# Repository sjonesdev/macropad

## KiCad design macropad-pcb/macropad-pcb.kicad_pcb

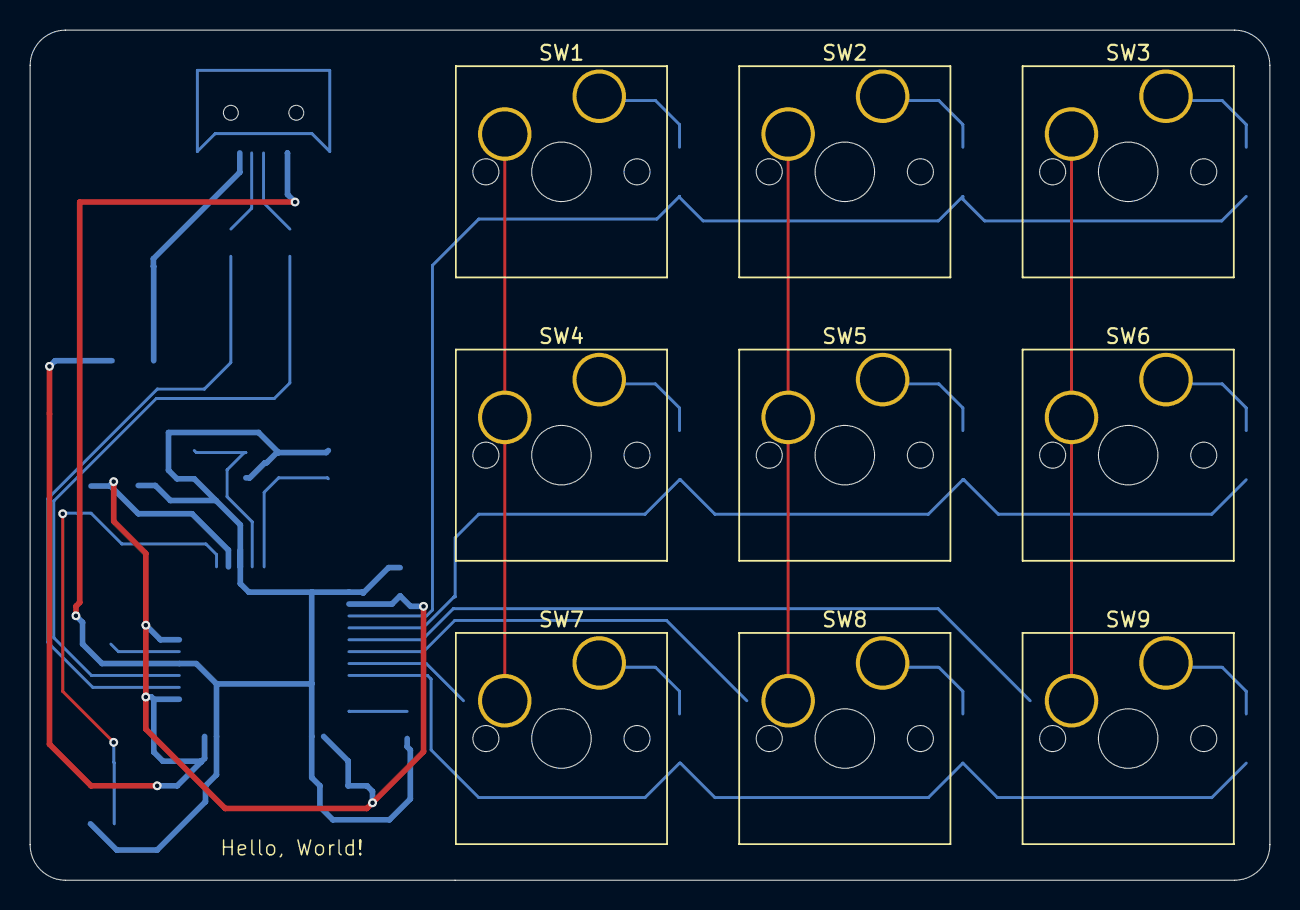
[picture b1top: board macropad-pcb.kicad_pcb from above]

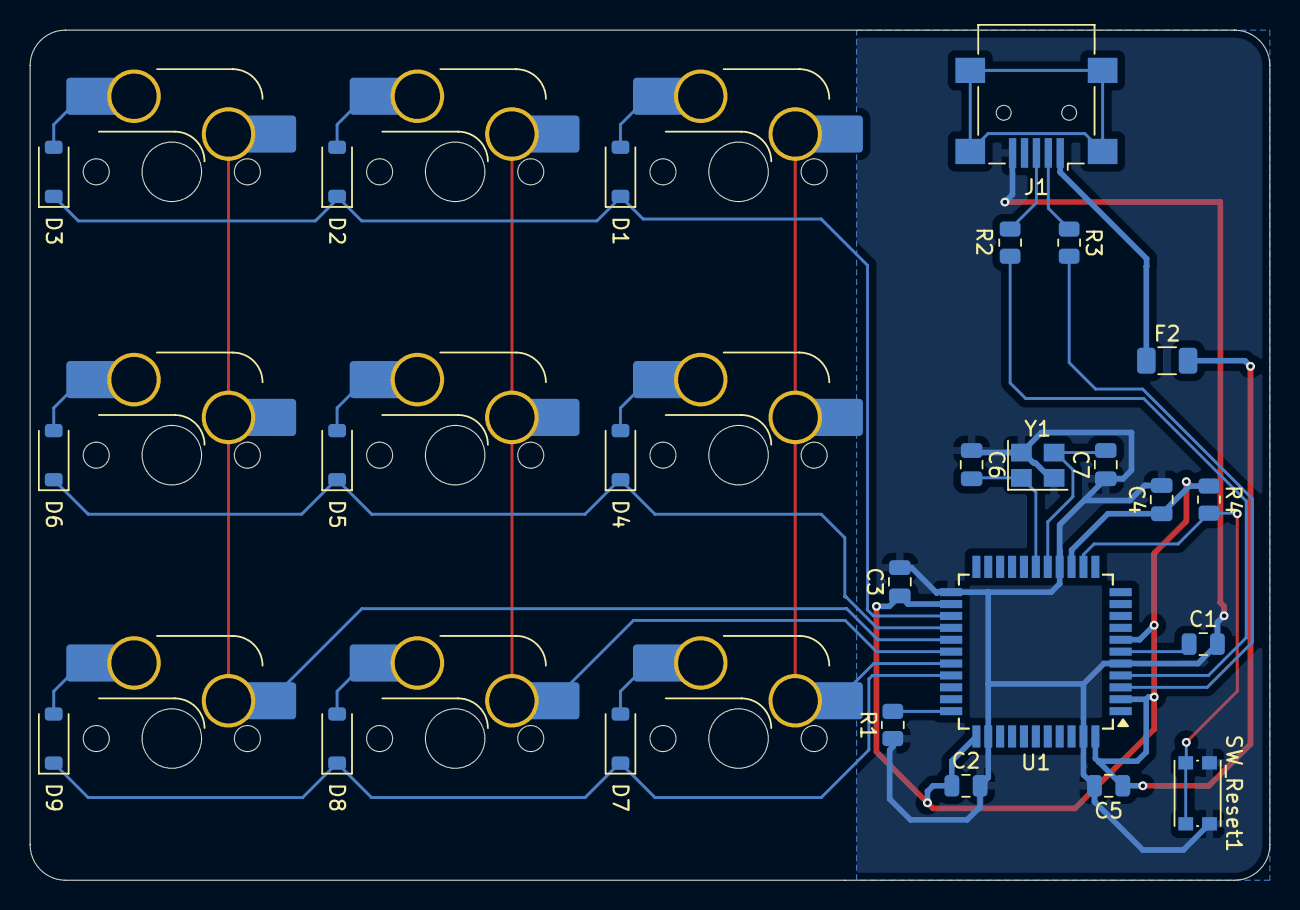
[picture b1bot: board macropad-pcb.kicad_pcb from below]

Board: 2 copper layers, 83.3 x 57.2 mm, 34 parts (25 on the bottom side), 27 nets.

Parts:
C1: 1uF; C_0805_2012Metric
C2, C3, C4: 0.1uF; C_0805_2012Metric
C5: 10uF; C_0805_2012Metric
C6, C7: 22pF; C_0805_2012Metric
D1, D2, D3, D4, D5, D6, D7, D8, D9: D_Small; D_SOD-123
F2: 500mA; Fuse_1206_3216Metric
J1: USB_B_Mini; USB_Mini-B_Lumberg_2486_01_Horizontal
R1, R4: 10k; R_0805_2012Metric
R2, R3: 22; R_0805_2012Metric
SW1, SW2, SW3, SW4, SW5, SW6, SW7, SW8, SW9: SW_Push; SW_Hotswap_Kailh_MX_Plated_1.00u
SW_Reset1: SW_Push; SW_Push_1P1T_NO_CK_KMR2
U1: ATmega32U4-A; TQFP-44_10x10mm_P0.8mm
Y1: 16MHz; Crystal_SMD_3225-4Pin_3.2x2.5mm

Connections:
+5V: C2.1, C3.1, C4.1, C5.1, F2.2, R4.1, U1.2 (UVCC), U1.7 (VBUS), U1.14 (VCC), U1.24 (AVCC), U1.34 (VCC), U1.44 (AVCC)
/Col0: SW1.1, SW4.1, SW7.1, U1.29 (PB5)
/Col1: SW2.1, SW5.1, SW8.1, U1.28 (PB4)
/Col2: SW3.1, SW6.1, SW9.1, U1.27 (PD7)
/D+: J1.3 (D+), R2.1
/D-: J1.2 (D-), R3.1
/Row0: D1.1 (K), D2.1 (K), D3.1 (K), U1.25 (PD4)
/Row1: D4.1 (K), D5.1 (K), D6.1 (K), U1.26 (PD6)
/Row2: D7.1 (K), D8.1 (K), D9.1 (K), U1.30 (PB6)
GND: C1.2, C2.2, C3.2, C4.2, C5.2, C6.1, C7.1, J1.5 (GND), R1.1, SW_Reset1.1, U1.5 (UGND), U1.15 (GND), U1.23 (GND), U1.35 (GND), U1.43 (GND), Y1.2, Y1.4
unnamed: D1.2 (A), SW1.2
unnamed: D2.2 (A), SW2.2
unnamed: D3.2 (A), SW3.2
unnamed: D4.2 (A), SW4.2
unnamed: D5.2 (A), SW5.2
unnamed: D6.2 (A), SW6.2
unnamed: D7.2 (A), SW7.2
unnamed: D8.2 (A), SW8.2
unnamed: D9.2 (A), SW9.2
unnamed: R2.2, U1.4 (D+)
unnamed: R3.2, U1.3 (D-)
unnamed: C1.1, U1.6 (UCAP)
unnamed: C6.2, U1.17 (XTAL1), Y1.1
unnamed: C7.2, U1.16 (XTAL2), Y1.3
unnamed: R1.2, U1.33 (~HWB/PE2)
unnamed: R4.2, SW_Reset1.2, U1.13 (~RESET)
VCC: F2.1, J1.1 (VBUS)

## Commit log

2025-01-03 created kicad project
2025-01-03 added component library submodule
2025-01-03 added footprint library submodule
2025-01-03 added switch footprint library submodule
2025-01-03 removed old libs and added ones from tutorial (newer)
2025-01-07 added schematic for 3x3 macropad
2025-01-07 removed libraries in favor of using libraries straight from kicad, removed tracking of backups folder in version control, created and routed pcb
2025-01-07 added gnd net fill
2025-01-07 changed to just mx footprint since i haven't figured out how to handle the annular width issue of the hybrid footprint and made output files
